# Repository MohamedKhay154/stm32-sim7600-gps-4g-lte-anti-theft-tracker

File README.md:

# STM32 SIM7600 GPS Tracker

This hobby project is designed to be a practical gadget that can be used in daily life, whether you own an expensive bike or car and want to detect theft once it is parked, or simply want to track anything using GPS and cloud connectivity. 
In this project, I will explain how I developed and built the system.

---

# Overview

The STM32 communicates with the SIM7600E module via UART. GPS data is parsed on the MCU and sent either via SMS or published to an MQTT broker. Node-RED processes incoming data and provides visualization and control.

---

# Features

- Custom PCB design
- GPS tracking
- MQTT publish/subscribe
- Geofence/Park mode
- Connection health monitoring
- Modular embedded software design

---

# Hardware
Since this project is intended to be a compact GPS tracker, I wanted to make it as small as possible while using the SIM7600E module. I decided to divide the hardware into two separate PCBs.

The first PCB contains the SIM7600E module and all the required supporting hardware, such as the SIM card holder, antennas, and its dedicated voltage regulator. The second PCB contains the STM32L072 microcontroller and the remaining supporting hardware components. Both PCBs are stacked together and communicate through a common connector interface.

Note: In this page, I will only discuss the SIM7600E board because the second board is still under development. I am currently adding extra features to it, such as a battery charging circuit and a gyroscope. Once it is completed, I will publish it as well. For now, I am using a Nucleo board for prototyping.

## Schematic

The first main step in designing a custom PCB is creating the schematic. The datasheet provided by SIMCom was very helpful, as it includes recommended circuits and components, which made the design process much simpler.

I used the same buck converter recommended in the datasheet, the LM2596S-ADJ, because the board is powered using a 2S LiPo battery, which can provide up to 8.4V when fully charged and around 7.4V typically.

A logic level shifter is used to convert the SIM7600E 1.8V logic levels to 3.3V logic levels, ensuring safe UART communication with the microcontroller.

For the antennas, I chose a much simpler design, except for the GPS antenna, which requires a so-called bias-tee circuit to properly power the active GPS antenna. This circuit was also recommended and explained in the SIMCom datasheet.

Some LEDs were also added to visualize the network status.

In general, the SIM7600E supports many additional features, such as an SD card interface, but I only implemented the features that were necessary for this project.

## Footprints and Layout

After reviewing the schematic, the next step is selecting the appropriate footprints. I have included the footprints I used, along with the symbols and 3D models, in the folder PCB Design/SIM7600E.

If this is your first time designing a PCB, like it was for me, avoid making the same mistake I did by choosing footprints that are too small for resistors, capacitors, and LEDs, especially if you plan to solder the board yourself.

For the PCB layout, I chose a 4-layer design to improve performance. The two inner layers are dedicated to the ground plane and power plane. 

This step is very important because a good PCB layout greatly affects the overall performance of the board, especially for the buck converter and high-frequency signals. 

## Manufacturing 

I ordered the PCB from JLCPCB and the components from LCSC, then soldered the board myself.

The BOM and component position files can be found here: `PCB Design/SIM7600E/production`

---

# Software Architecture

## Main Modules

```text
Core/
├── Inc/
  ├── min.h
  ├── SIM7600E.h
  ├── system_fsm.h
  ├── timer.h
  └── log.h
├── Src/
  ├── min.c
  ├── SIM7600E.c
  ├── system_fsm.c
  └── timer.c
```

`SIM7600.h` and `SIM7600.c` contain all the required functions to communicate with the SIM7600E module using UART, including GPS positioning, power control, SMS handling, and MQTT publish/subscribe functionality.

`system_fsm.h` and `system_fsm.c` contain the implementation of the finite state machine, which will be explained in the next section.

`timer.h` and `timer.c` contain the functions related to the timers used for tracking and system monitoring.

`log.h` contains an overridden version of the `printf` function used for logging general information, errors, and communication between the STM32 and the SIM7600E module for debugging purposes.

### Example of the logging interface during the TRACKING state.

---

# State Machine

The firmware uses an event-driven finite state machine.

## States

- CONNECT
- IDLE
- TRACK
- PARK

## Description

The CONNECT state is responsible for checking the status of the system components. It verifies whether the SIM module is powered, whether the network and MQTT connection are established, and whether the GPS is enabled. If any component is not ready, the state attempts to initialize or reconnect it accordingly. Once everything is ready, the system transitions to the IDLE state, where it waits for incoming events or commands.

If a `WHERE` command is received, the device immediately sends its current GPS position.

If a `TRACK` command is received, the system transitions to the TRACK state. In this state, a timer is started, and the device periodically sends its GPS position until a `STOP` command is received, after which the system returns to the IDLE state.

If a `PARK` command is received, the system transitions to the PARK state. First, the current GPS position is sent in order to create a geofence around the parked location (explained later in the Node-RED section). A timer is then started to continuously monitor the device position. If a geofence breach occurs, meaning the tracked device moves away from the allowed area, an alert is sent and the system automatically switches to TRACK mode since this may indicate a potential theft attempt.

In all states, another timer called `sysHealth_Timer` runs every 5 seconds to monitor the health of the communication stack. If a connection loss is detected in any state, the system automatically transitions back to the CONNECT state to recover the connection and then returns to the previous operational state.

## Why State Machine ?

Since this project is intended to work as an anti-theft tracker, it contains several different states and operating modes. Using a state machine makes the system more organized, prevents illogical scenarios, and makes the firmware easier to extend in the future.

For example, new subtasks, events, or operating modes can be added more easily. I also plan to allow the user to select these modes through hardware buttons, so having a state-machine-based architecture will make this feature easier to implement later.

---
# Node-Red

Node-RED is widely used in IoT and network-related applications, and it supports the MQTT protocol natively. In addition, it is very easy to use and implement thanks to its drag-and-drop interface and simple JavaScript programming.

Node-RED subscribes to the same MQTT topic used by the SIM7600E module, receives the GPS position data, and then sends it as JSON data to a world map dashboard for visualization.

I also added support for different operating modes because each mode requires a specific type of visualization. For example, in TRACK mode, the system displays the traveled path, while in PARK mode, it creates a circular geofence around the parked position. The different visualizations are shown in the following pictures.

---

# Future Improvements

- Add a gyroscope/accelerometer for PARK mode in order to detect even the smallest movements. GPS data always has some tolerance and can sometimes vary by up to several meters, making it unreliable for immediate theft detection. By using a gyroscope or motion sensor, the system could instantly detect movement and then rely on GPS for long-distance tracking.
- Add a database to the Node-RED dashboard to give the project memory capabilities, allowing users to save and review previous trips, routes, and tracking history.
- Add battery monitoring functionality to the second PCB in order to monitor battery level and improve power management.

---

# Author

Mohamed Khay
Computer Engineering Student

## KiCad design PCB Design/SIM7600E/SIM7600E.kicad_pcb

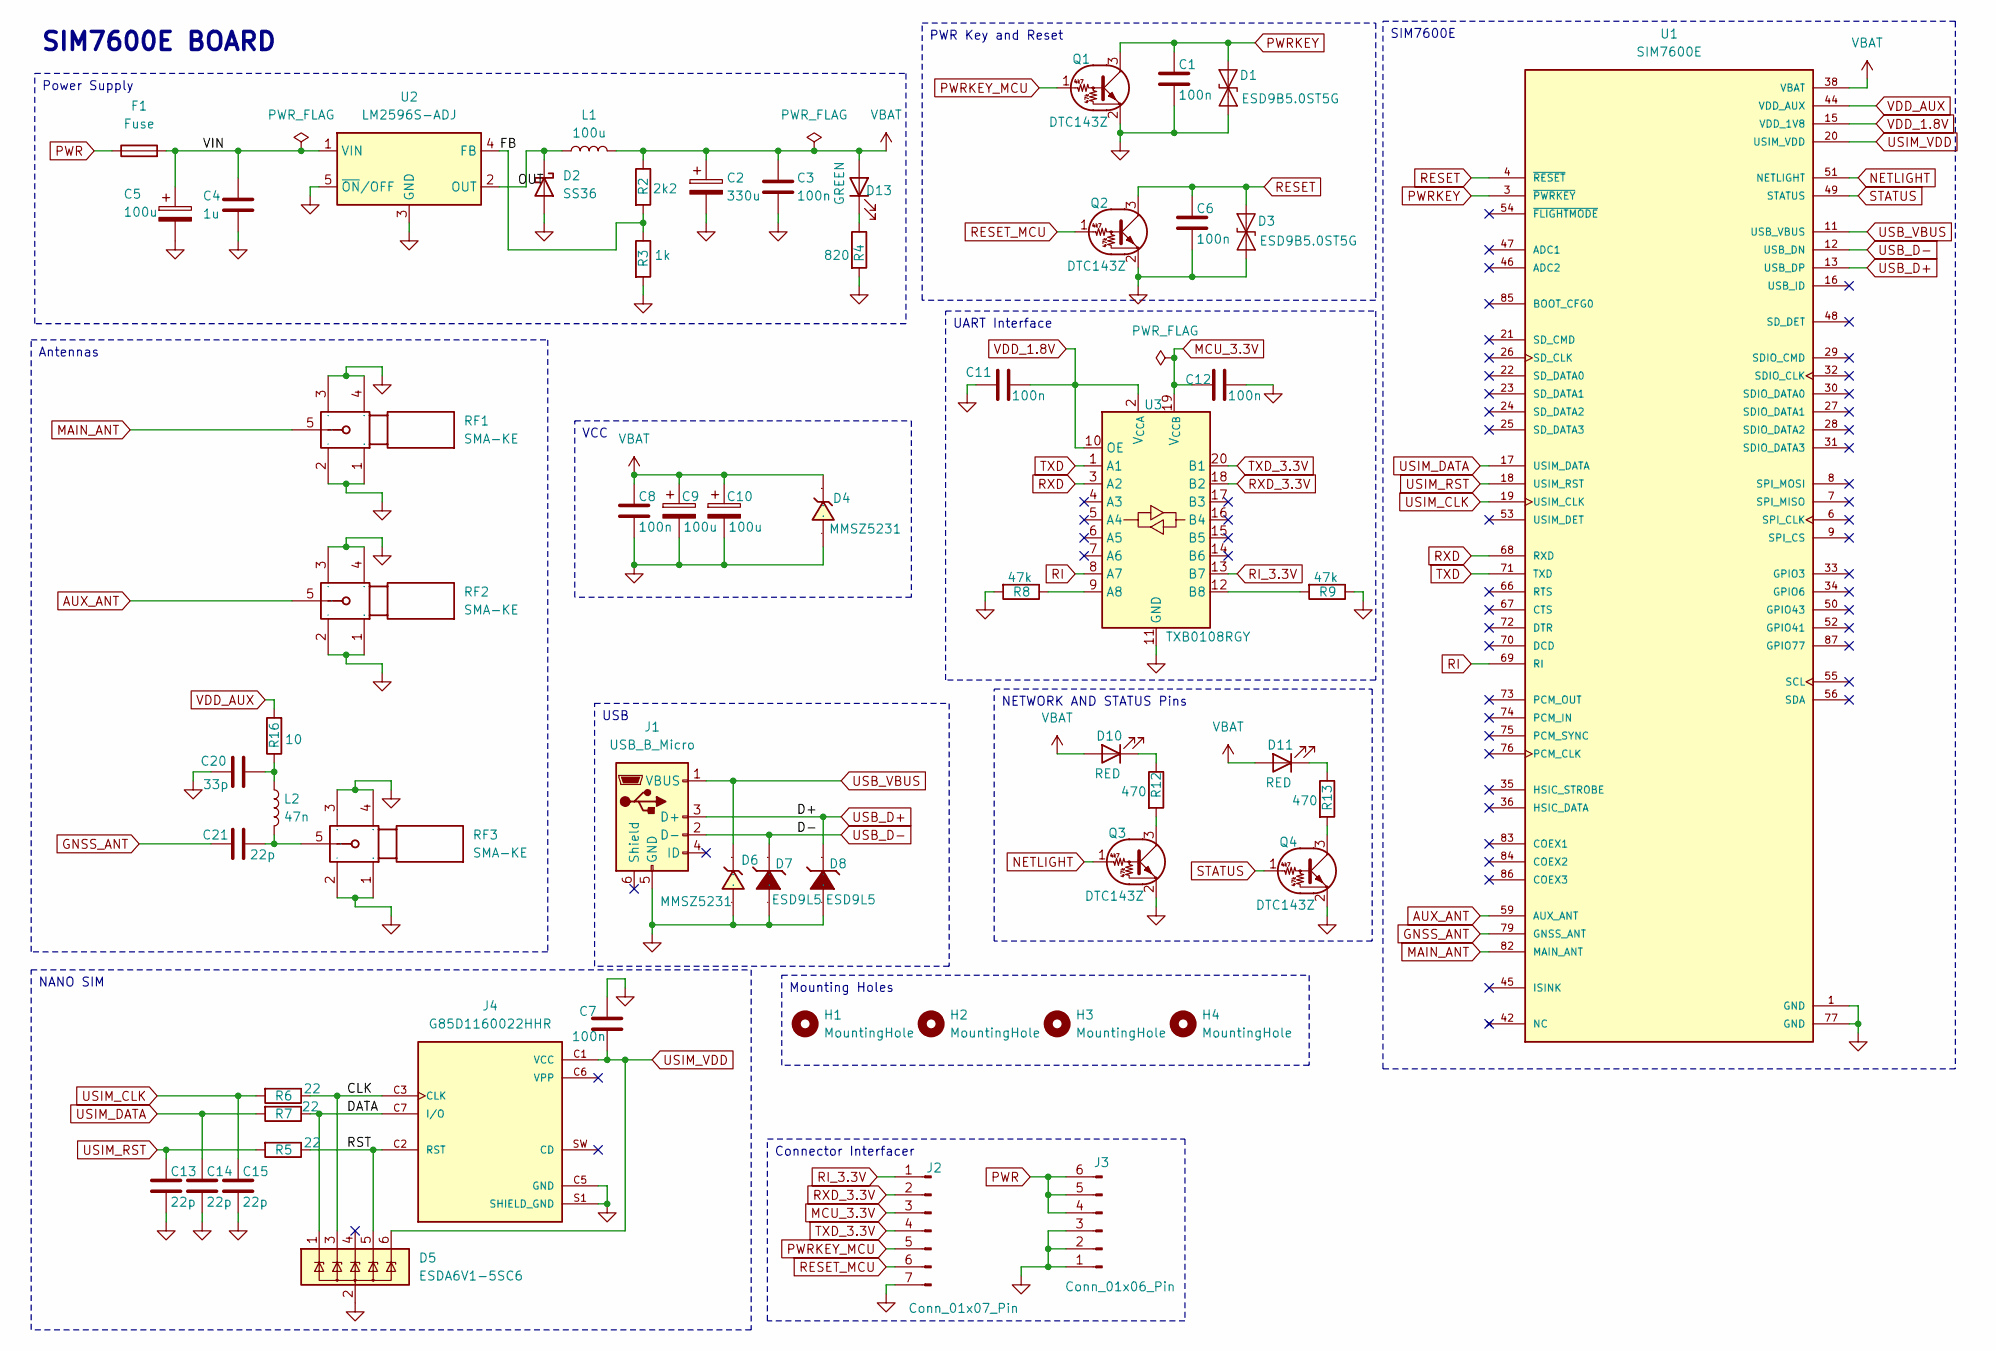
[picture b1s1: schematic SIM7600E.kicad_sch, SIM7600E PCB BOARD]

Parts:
C1, C3, C6, C7, C8, C11, C12: 100n; C_0603_1608Metric_Pad1.08x0.95mm_HandSolder
C2: 330u; CP_Elec_8x6.9; jlcpcb C3274687
C4: 1u; C_0603_1608Metric_Pad1.08x0.95mm_HandSolder
C5, C9, C10: 100u; CP_Elec_5x5.9; jlcpcb C542291
C13, C14, C15, C21: 22p; C_0603_1608Metric_Pad1.08x0.95mm_HandSolder
C20: 33p; C_0603_1608Metric_Pad1.08x0.95mm_HandSolder
D1, D3: ESD9B5.0ST5G; D_SOD-923
D2: SS36; D_SMA
D4, D6: MMSZ5231; SOD-123_L2.8-W1.8-LS3.7-RD; Manufacturer Part MMSZ5231BT1G
D5: ESDA6V1-5SC6; SOT-23-6_Handsoldering
D7, D8: ESD9L5; SOD-923_L0.8-W0.6-LS1.0-RD; Manufacturer Part ESD9L5.0ST5G
D10, D11: RED; LED_0603_1608Metric_Pad1.05x0.95mm_HandSolder; JLCPCB C7371906
D13: GREEN; LED_0603_1608Metric_Pad1.05x0.95mm_HandSolder; JLCPCB C7371905
F1: Fuse; Fuse_1206_3216Metric_Pad1.42x1.75mm_HandSolder
H1, H2, H3, H4: MountingHole; MountingHole_2.1mm
J1: USB_B_Micro; USB_Micro-B_Amphenol_10103594-0001LF_Horizontal
J2: Conn_01x07_Pin; PinHeader_1x07_P2.54mm_Vertical
J3: Conn_01x06_Pin; PinHeader_1x06_P2.54mm_Vertical
J4: G85D1160022HHR; AMPHENOL_G85D1160022HHR; PARTREV AX3; DigiKey_Part_Number 664-G85D1160022HHRCT-ND
L1: 100u; L_Vishay_IHLP-4040
L2: 47n; L_0603_1608Metric_Pad1.05x0.95mm_HandSolder; JLCPCB C98077
Q1, Q2, Q3, Q4: DTC143Z; SOT-23_Handsoldering; JLCPCB C15236
R2: 2k2; R_0603_1608Metric_Pad0.98x0.95mm_HandSolder
R3: 1k; R_0603_1608Metric_Pad0.98x0.95mm_HandSolder
R4: 820; R_0603_1608Metric_Pad0.98x0.95mm_HandSolder
R5, R6, R7: 22; R_0603_1608Metric_Pad0.98x0.95mm_HandSolder
R8, R9: 47k; R_0603_1608Metric_Pad0.98x0.95mm_HandSolder
R12, R13: 470; R_0603_1608Metric_Pad0.98x0.95mm_HandSolder
R16: 10; R_0603_1608Metric_Pad0.98x0.95mm_HandSolder
RF1, RF2, RF3: SMA-KE; SMA-TH_SMA-KE-5; Manufacturer Part SMA-KE-5
U1: SIM7600E; XCVR_SIM7600E; PARTREV V1.03
U2: LM2596S-ADJ; TO-263-5_TabPin3; JLCPCB C5349987
U3: TXB0108RGY; Texas_RGY_R-PVQFN-N20_EP2.05x3.05mm

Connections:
/CLK: D5.3 (IO2), J4.C3 (CLK), R6.1
/DATA: D5.1 (IO1), J4.C7 (I/O), R7.1
/FB: R2.2, R3.1, U2.4 (FB)
/OUT: D2.1 (K), L1.1, U2.2 (OUT)
/RST: D5.5 (IO4), J4.C2 (RST), R5.1
/VIN: C4.1, C5.1, F1.2, U2.1 (VIN)
AUX_ANT: RF2.5, U1.59 (AUX_ANT)
GND: C1.2, C2.2, C3.2, C4.2, C5.2, C6.2, C7.1, C8.2, C9.2, C10.2, C11.1, C12.2, C13.2, C14.2, C15.2, C20.1, D1.1 (A1), D2.2 (A), D3.1 (A1), D4.2 (A), D5.2 (GND), D6.2 (A), D7.2 (A), D8.2 (A), J1.5 (GND), J2.7, J3.1, J3.2, J3.3, J4.C5 (GND), J4.S1 (SHIELD_GND), J4.S2 (SHIELD_GND), J4.S3 (SHIELD_GND), Q1.2 (E), Q2.2 (E), Q3.2 (E), Q4.2 (E), R3.2, R4.2, R8.2, R9.1, RF1.1, RF1.2, RF1.3, RF1.4, RF2.1, RF2.2, RF2.3, RF2.4, RF3.1, RF3.2, RF3.3, RF3.4, U1.1 (GND), U1.2 (GND1), U1.5 (GND1), U1.10 (GND1), U1.14 (GND1), U1.37 (GND1), U1.40 (GND1), U1.41 (GND1), U1.43 (GND1), U1.57 (GND1), U1.58 (GND1), U1.60 (GND1), U1.61 (GND1), U1.64 (GND1), U1.65 (GND1), U1.77 (GND), U1.78 (GND2), U1.80 (GND2), U1.81 (GND2), U2.3 (GND), U2.5 (~ON/OFF), U3.11 (GND), U3.21 (GND)
GNSS_ANT: C21.1, U1.79 (GNSS_ANT)
MAIN_ANT: RF1.5, U1.82 (MAIN_ANT)
MCU_3.3V: C12.1, J2.3, U3.19 (V_{CCB})
NETLIGHT: Q3.1 (B), U1.51 (NETLIGHT)
unnamed: C20.2, L2.1, R16.1
unnamed: C21.2, L2.2, RF3.5
unnamed: D10.1 (K), R12.1
unnamed: D11.1 (K), R13.1
unnamed: D13.1 (K), R4.1
unnamed: Q3.3 (C), R12.2
unnamed: Q4.3 (C), R13.2
unnamed: R8.1, U3.9 (A8)
unnamed: R9.2, U3.12 (B8)
PWR: F1.1, J3.4, J3.5, J3.6
PWRKEY: C1.1, D1.2 (A2), Q1.3 (C), U1.3 (~PWRKEY)
PWRKEY_MCU: J2.5, Q1.1 (B)
RESET: C6.1, D3.2 (A2), Q2.3 (C), U1.4 (~RESET)
RESET_MCU: J2.6, Q2.1 (B)
RI: U1.69 (RI), U3.8 (A7)
RI_3.3V: J2.1, U3.13 (B7)
RXD: U1.68 (RXD), U3.3 (A2)
RXD_3.3V: J2.2, U3.18 (B2)
STATUS: Q4.1 (B), U1.49 (STATUS)
TXD: U1.71 (TXD), U3.1 (A1)
TXD_3.3V: J2.4, U3.20 (B1)
USB_D+: D8.1 (C), J1.3 (D+), U1.13 (USB_DP)
USB_D-: D7.1 (C), J1.2 (D-), U1.12 (USB_DN)
USB_VBUS: D6.1 (K), J1.1 (VBUS), U1.11 (USB_VBUS)
USIM_CLK: C15.1, R6.2, U1.19 (USIM_CLK)
USIM_DATA: C14.1, R7.2, U1.17 (USIM_DATA)
USIM_RST: C13.1, R5.2, U1.18 (USIM_RST)
USIM_VDD: C7.2, D5.6 (IO5), J4.C1 (VCC), U1.20 (USIM_VDD)
VBAT: C2.1, C3.1, C8.1, C9.1, C10.1, D4.1 (K), D10.2 (A), D11.2 (A), D13.2 (A), L1.2, R2.1, U1.38 (VBAT), U1.39 (VBAT), U1.62 (VBAT), U1.63 (VBAT)
VDD_1.8V: C11.2, U1.15 (VDD_1V8), U3.2 (V_{CCA}), U3.10 (OE)
VDD_AUX: R16.2, U1.44 (VDD_AUX)

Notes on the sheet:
SIM7600E BOARD
PWR Key and Reset
SIM7600E
Antennas
NANO SIM
NETWORK AND STATUS Pins
UART Interface
VCC
USB
Connector Interfacer
Mounting Holes
Power Supply

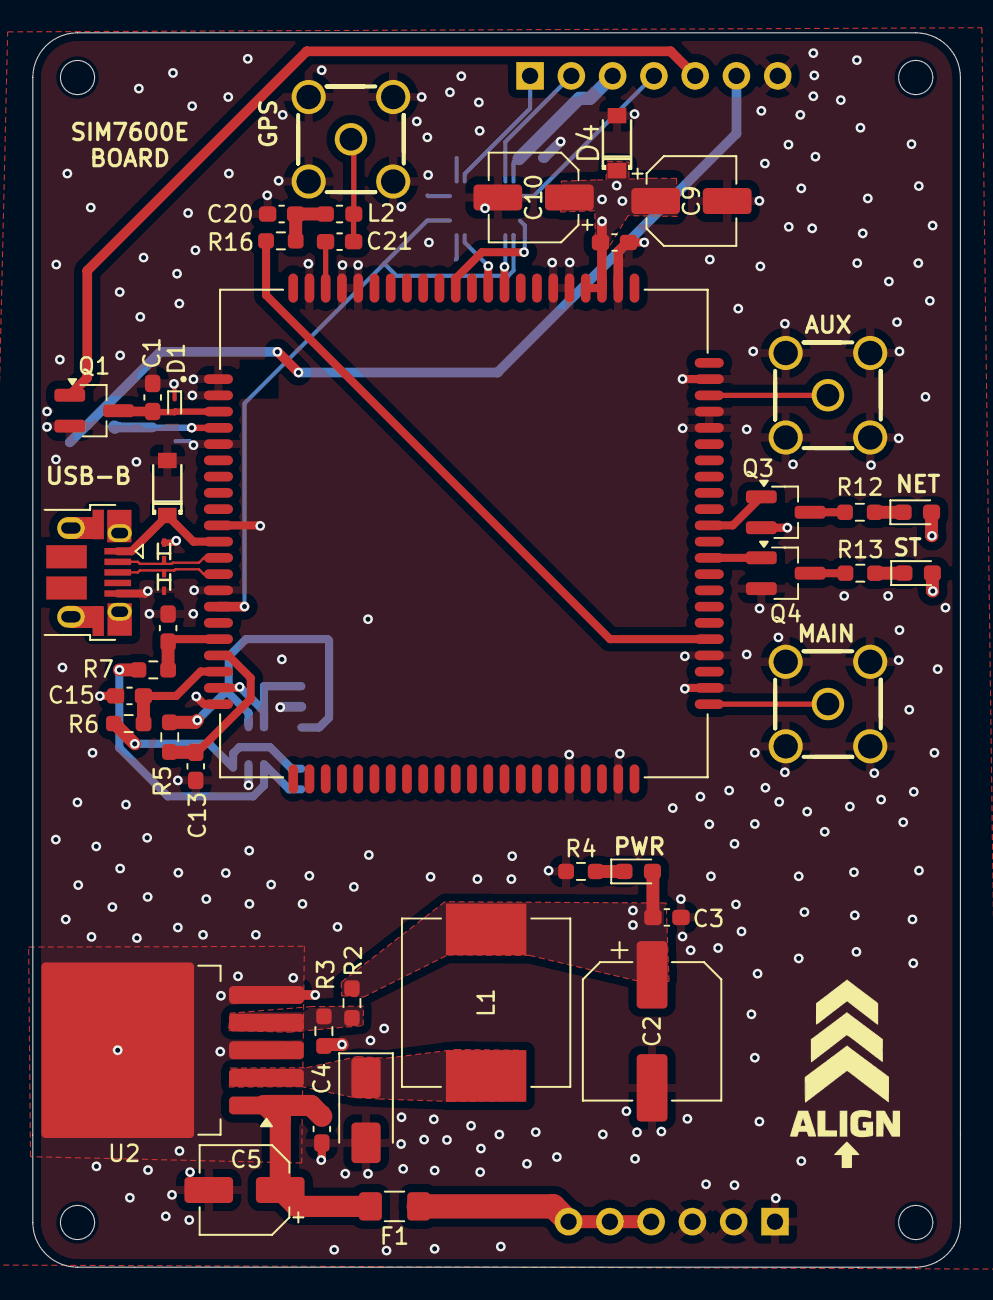
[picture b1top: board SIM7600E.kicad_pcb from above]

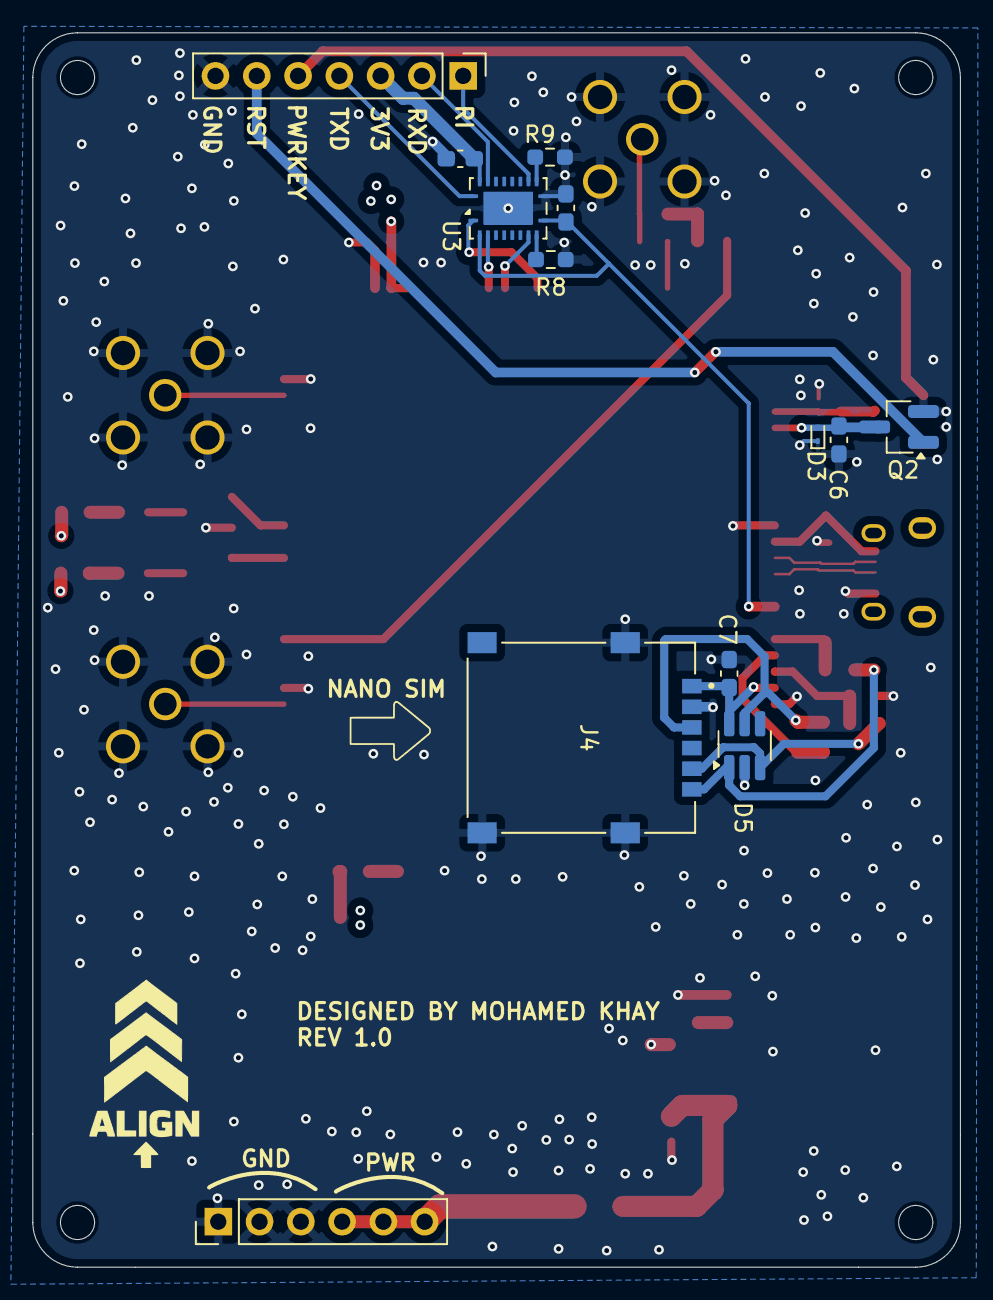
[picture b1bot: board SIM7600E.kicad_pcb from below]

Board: 4 copper layers, 57.1 x 76.0 mm, 60 parts (13 on the bottom side), 43 nets.

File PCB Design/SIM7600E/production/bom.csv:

Designator,Footprint,Quantity,Value,LCSC Part #
"C1, C11, C12, C3, C6, C7, C8",0603,7,100n,
"C10, C5, C9",CP_Elec_5x5.9,3,100u,
"C13, C14, C15, C21",0603,4,22p,
C2,CP_Elec_8x6.9,1,330u,
C20,0603,1,33p,
C4,0603,1,1u,
"D1, D3",D_SOD-923,2,ESD9B5.0ST5G,
"D10, D11",0603,2,RED,
D13,0603,1,GREEN,
D2,D_SMA,1,SS36,
"D4, D6",SOD-123_L2.8-W1.8-LS3.7-RD,2,MMSZ5231,
D5,SOT-23-6_Handsoldering,1,ESDA6V1-5SC6,
"D7, D8",SOD-923_L0.8-W0.6-LS1.0-RD,2,ESD9L5,
F1,1206,1,Fuse,
J1,USB_Micro-B_Amphenol_10103594-0001LF_Horizontal,1,USB_B_Micro,
J2,PinHeader_1x07_P2.54mm_Vertical,1,Conn_01x07_Pin,
J3,PinHeader_1x06_P2.54mm_Vertical,1,Conn_01x06_Pin,
J4,AMPHENOL_G85D1160022HHR,1,G85D1160022HHR,
L1,L_Vishay_IHLP-4040,1,100u,
L2,0603,1,47n,
"Q1, Q2, Q3, Q4",SOT-23_Handsoldering,4,DTC143Z,
"R12, R13",0603,2,470,
R16,0603,1,10,
R2,0603,1,2k2,
R3,0603,1,1k,
R4,0603,1,820,
"R5, R6, R7",0603,3,22,
"R8, R9",0603,2,47k,
"RF1, RF2, RF3",SMA-TH_SMA-KE-5,3,SMA-KE,
U1,XCVR_SIM7600E,1,SIM7600E,
U2,TO-263-5_TabPin3,1,LM2596S-ADJ,
U3,Texas_RGY_R-PVQFN-N20_EP2.05x3.05mm,1,TXB0108RGY,

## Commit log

2026-05-11 Added Timer / FSM Repair
2026-05-11 pcb files upload
2026-05-11 pictures
2026-05-11 Rename node red flow.png to node_red_flow.png
